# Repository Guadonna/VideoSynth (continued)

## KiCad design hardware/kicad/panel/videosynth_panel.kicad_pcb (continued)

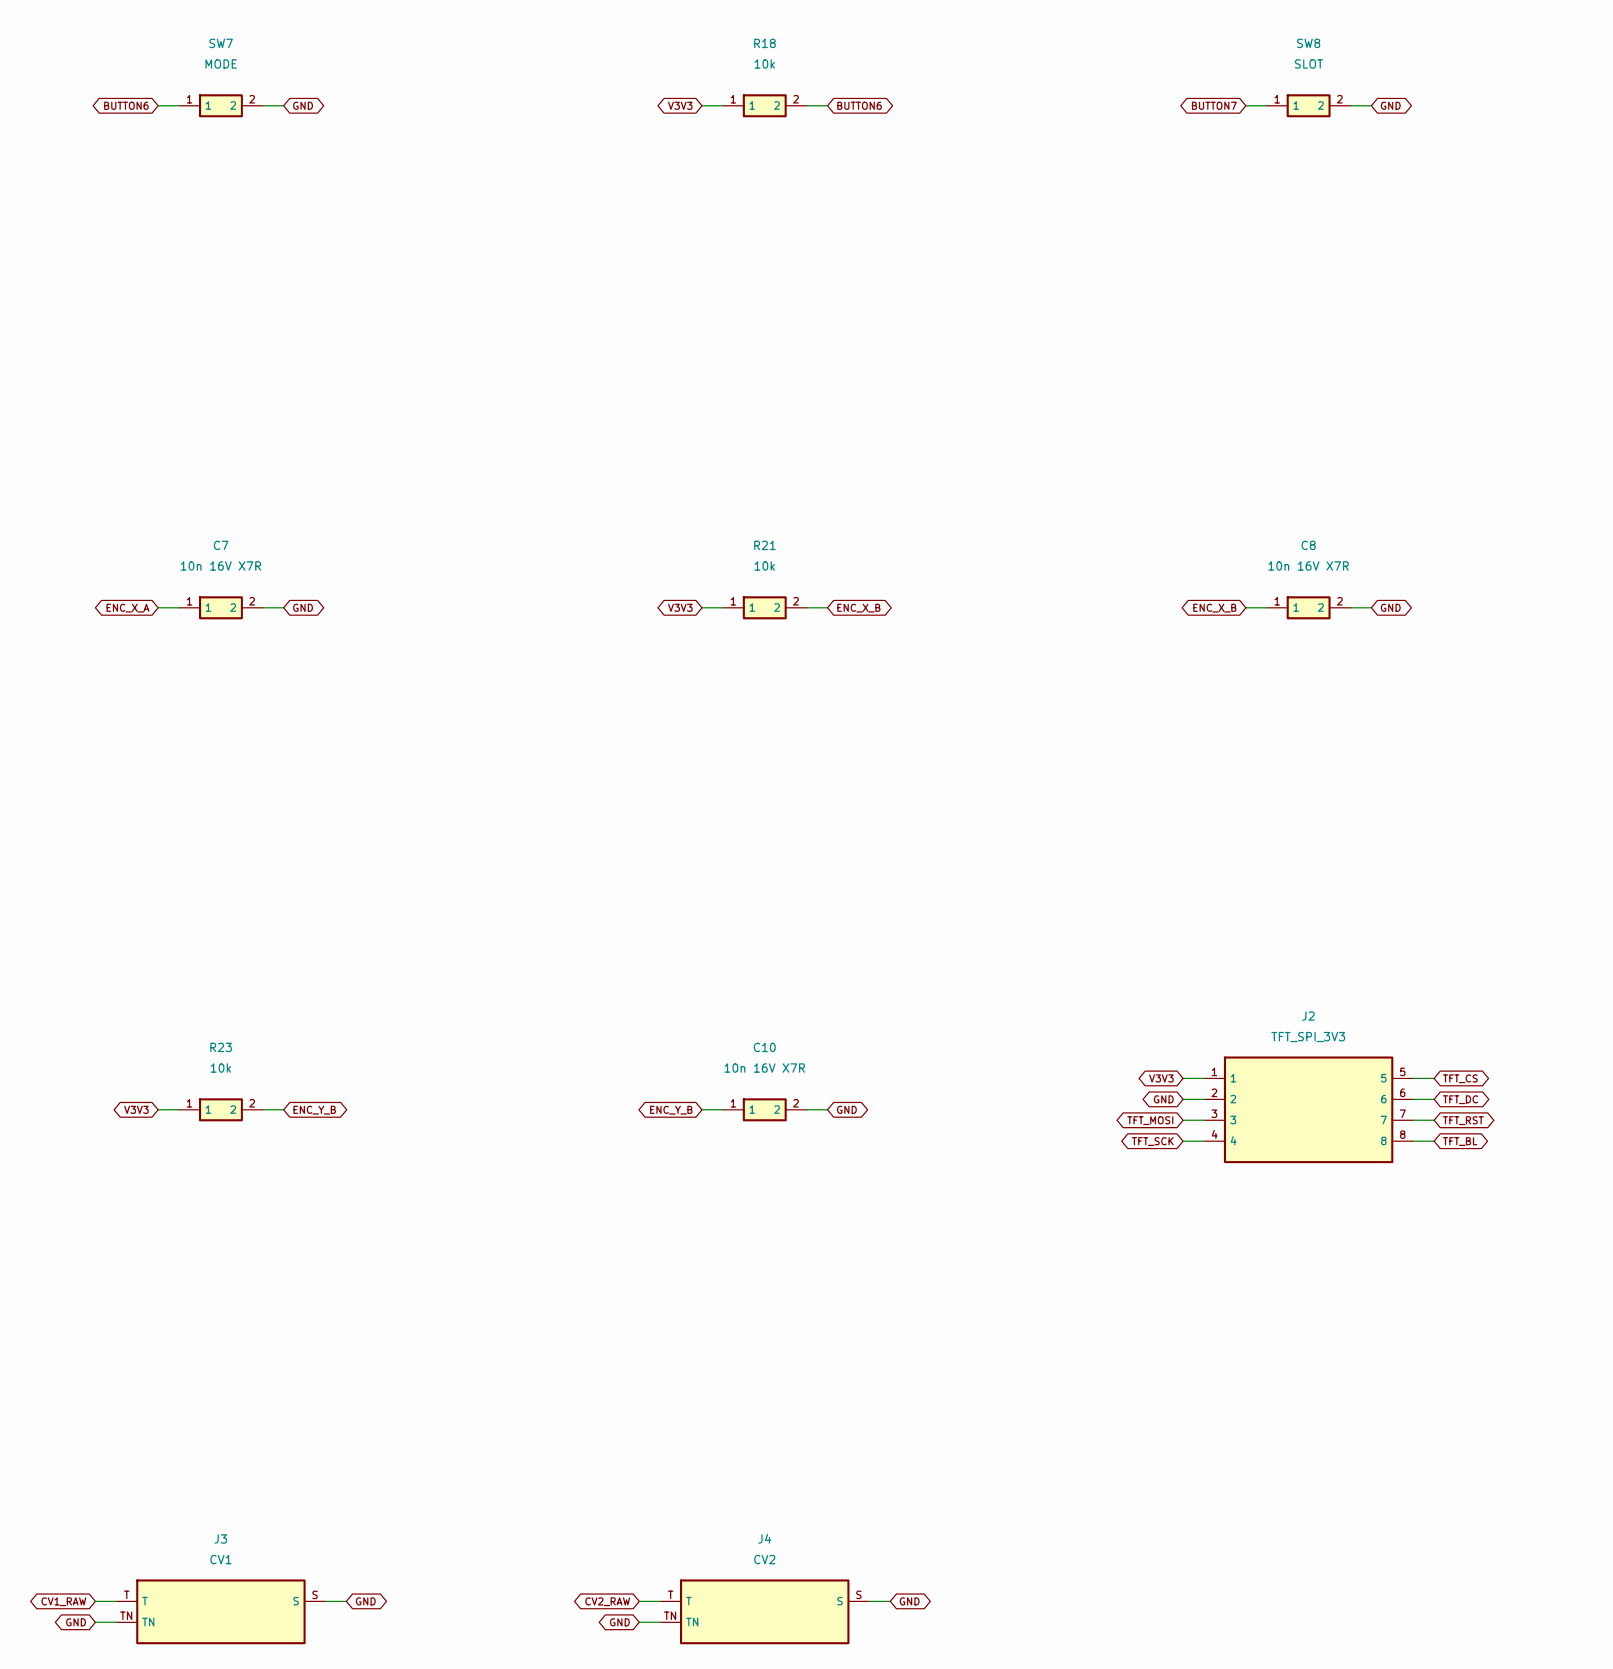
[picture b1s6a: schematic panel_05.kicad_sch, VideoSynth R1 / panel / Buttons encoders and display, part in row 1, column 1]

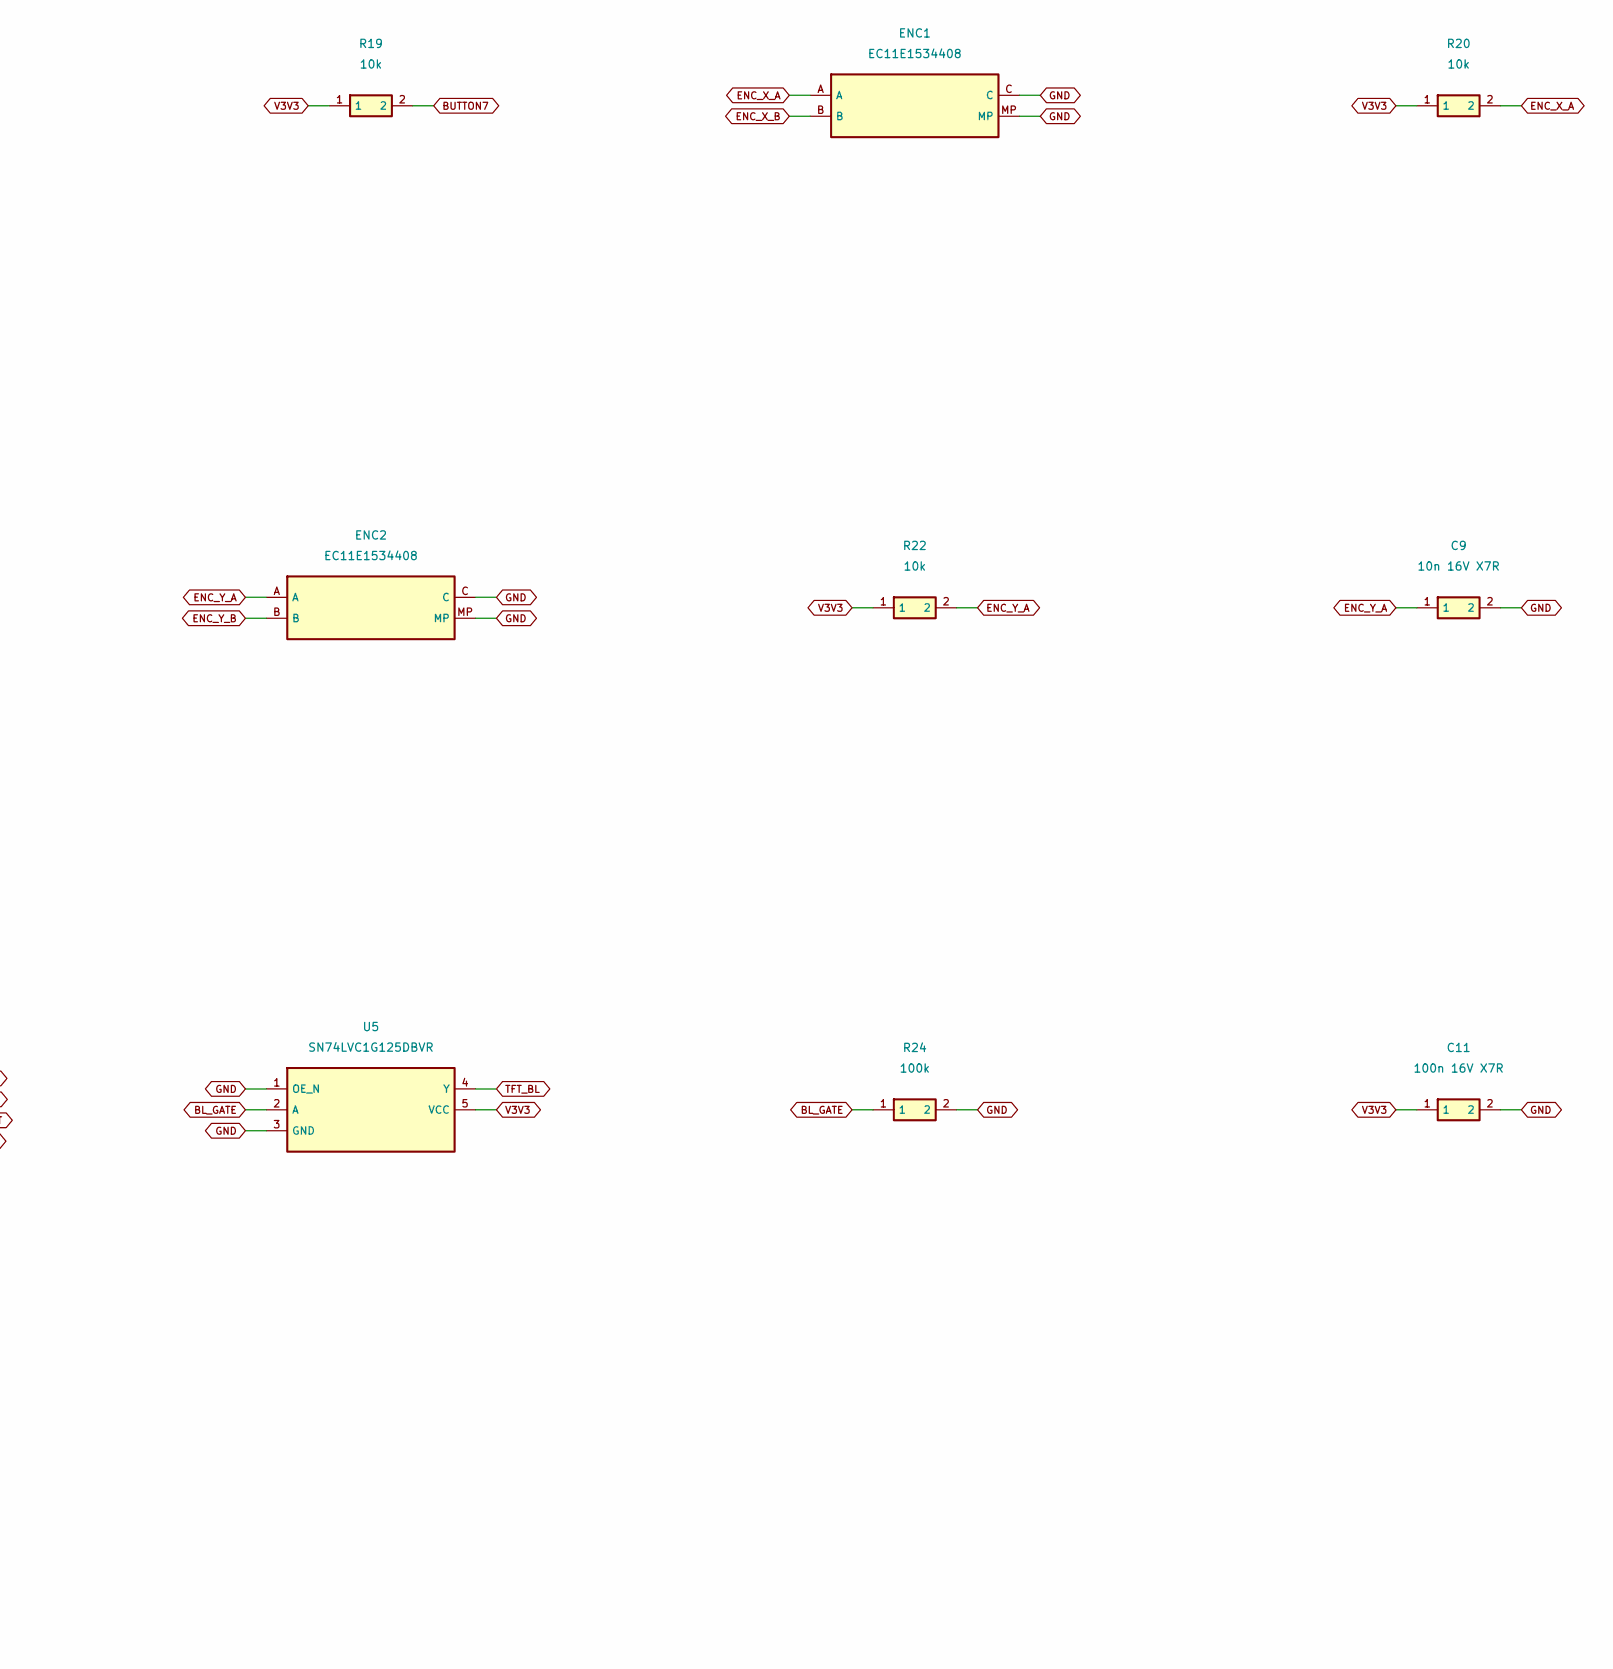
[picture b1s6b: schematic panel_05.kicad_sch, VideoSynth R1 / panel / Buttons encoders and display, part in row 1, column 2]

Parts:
C7, C8, C9, C10: 10n 16V X7R; C_0805_2012Metric
C11: 100n 16V X7R; C_0805_2012Metric
ENC1, ENC2: EC11E1534408; RotaryEncoder_Alps_EC11E_Vertical_H20mm
J2: TFT_SPI_3V3; PinHeader_1x08_P2.54mm_Vertical
J3: CV1; Jack_3.5mm_QingPu_WQP-PJ398SM_Vertical_CircularHoles
J4: CV2; Jack_3.5mm_QingPu_WQP-PJ398SM_Vertical_CircularHoles
R18, R19, R20, R21, R22, R23: 10k; R_0805_2012Metric
R24: 100k; R_0805_2012Metric
SW7: MODE; SW_PUSH_6mm
SW8: SLOT; SW_PUSH_6mm
U5: SN74LVC1G125DBVR; SOT-23-5

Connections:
BL_GATE: R24.1, U5.2 (A); also elsewhere on the board
BUTTON6: R18.2, SW7.1; also elsewhere on the board
BUTTON7: R19.2, SW8.1; also elsewhere on the board
CV1_RAW: J3.T; also elsewhere on the board
CV2_RAW: J4.T; also elsewhere on the board
ENC_X_A: C7.1, ENC1.A, R20.2; also elsewhere on the board
ENC_X_B: C8.1, ENC1.B, R21.2; also elsewhere on the board
ENC_Y_A: C9.1, ENC2.A, R22.2; also elsewhere on the board
ENC_Y_B: C10.1, ENC2.B, R23.2; also elsewhere on the board
GND: C7.2, C8.2, C9.2, C10.2, C11.2, ENC1.C, ENC1.MP, ENC2.C, ENC2.MP, J2.2, J3.S, J3.TN, J4.S, J4.TN, R24.2, SW7.2, SW8.2, U5.1 (OE_N), U5.3 (GND); also elsewhere on the board
TFT_BL: J2.8, U5.4 (Y)
TFT_CS: J2.5; also elsewhere on the board
TFT_DC: J2.6; also elsewhere on the board
TFT_MOSI: J2.3; also elsewhere on the board
TFT_RST: J2.7; also elsewhere on the board
TFT_SCK: J2.4; also elsewhere on the board
V3V3: C11.1, J2.1, R18.1, R19.1, R20.1, R21.1, R22.1, R23.1, U5.5 (VCC); also elsewhere on the board

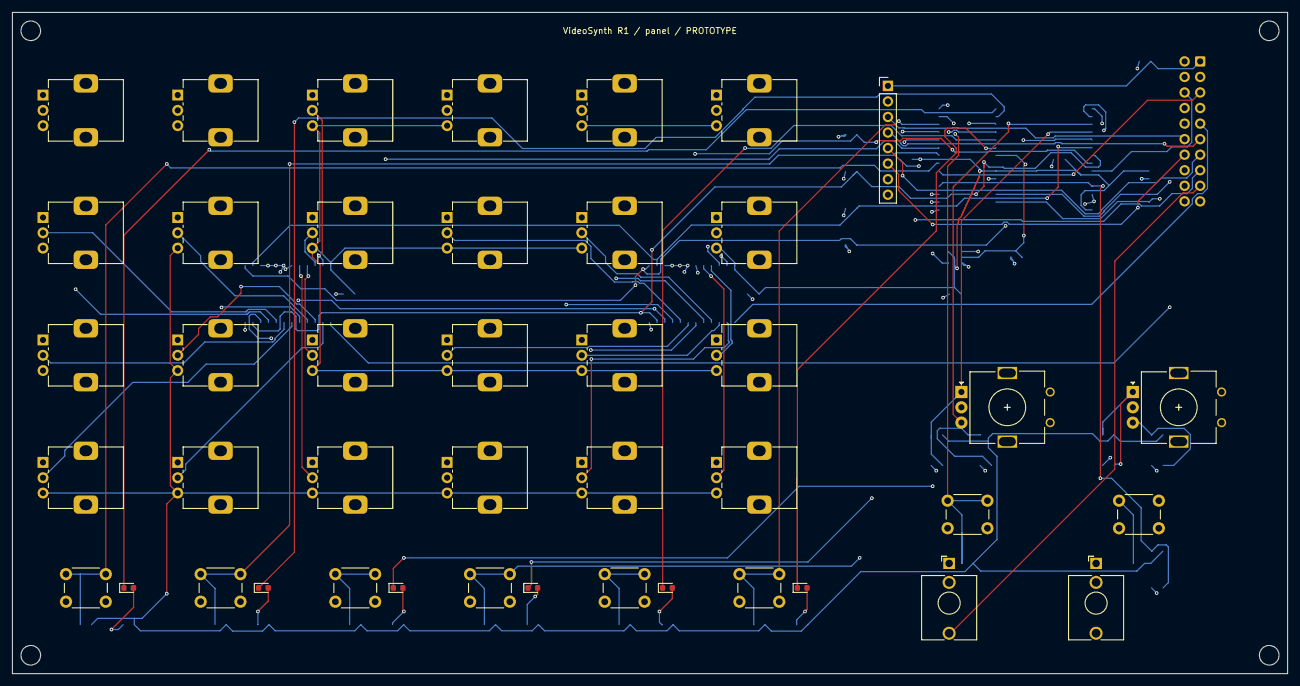
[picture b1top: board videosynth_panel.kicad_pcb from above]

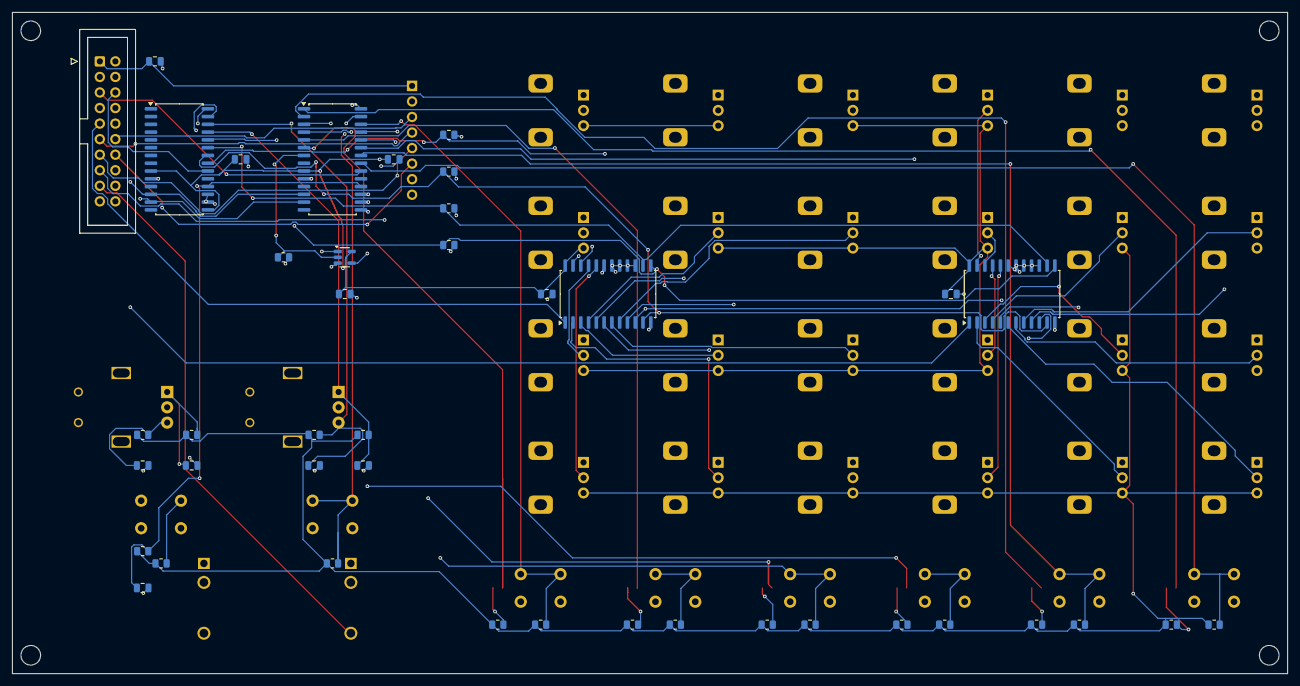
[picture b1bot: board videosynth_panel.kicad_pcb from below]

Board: 4 copper layers, 208.3 x 108.0 mm, 88 parts (41 on the bottom side), 70 nets.

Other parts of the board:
H1, H2, H3, H4: MountingHole_3.2mm_M3

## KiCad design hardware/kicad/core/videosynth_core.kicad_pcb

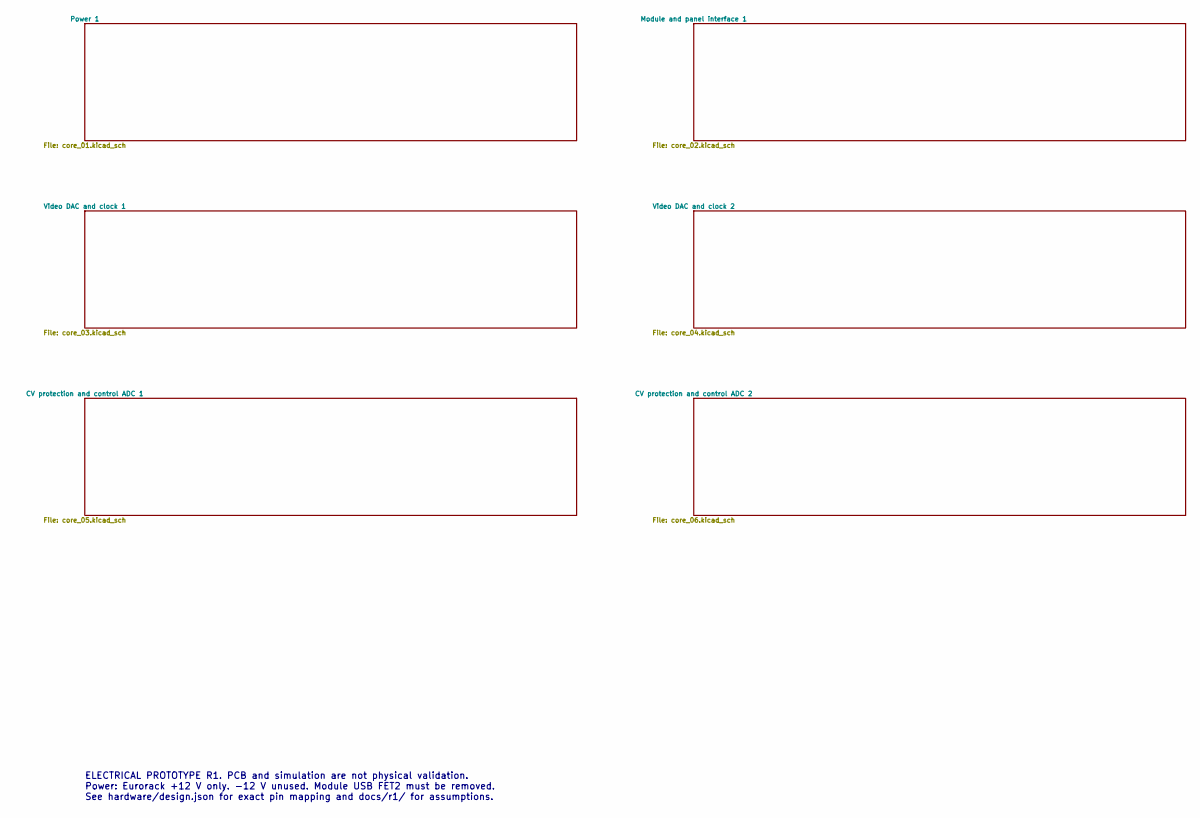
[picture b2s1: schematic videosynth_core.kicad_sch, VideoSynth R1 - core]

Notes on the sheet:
ELECTRICAL PROTOTYPE R1. PCB and simulation are not physical validation. Power: Eurorack +12 V only. -12 V unused. Module USB FET2 must be removed. See hardware/design.json for exact pin mapping and docs/r1/ for assumptions.

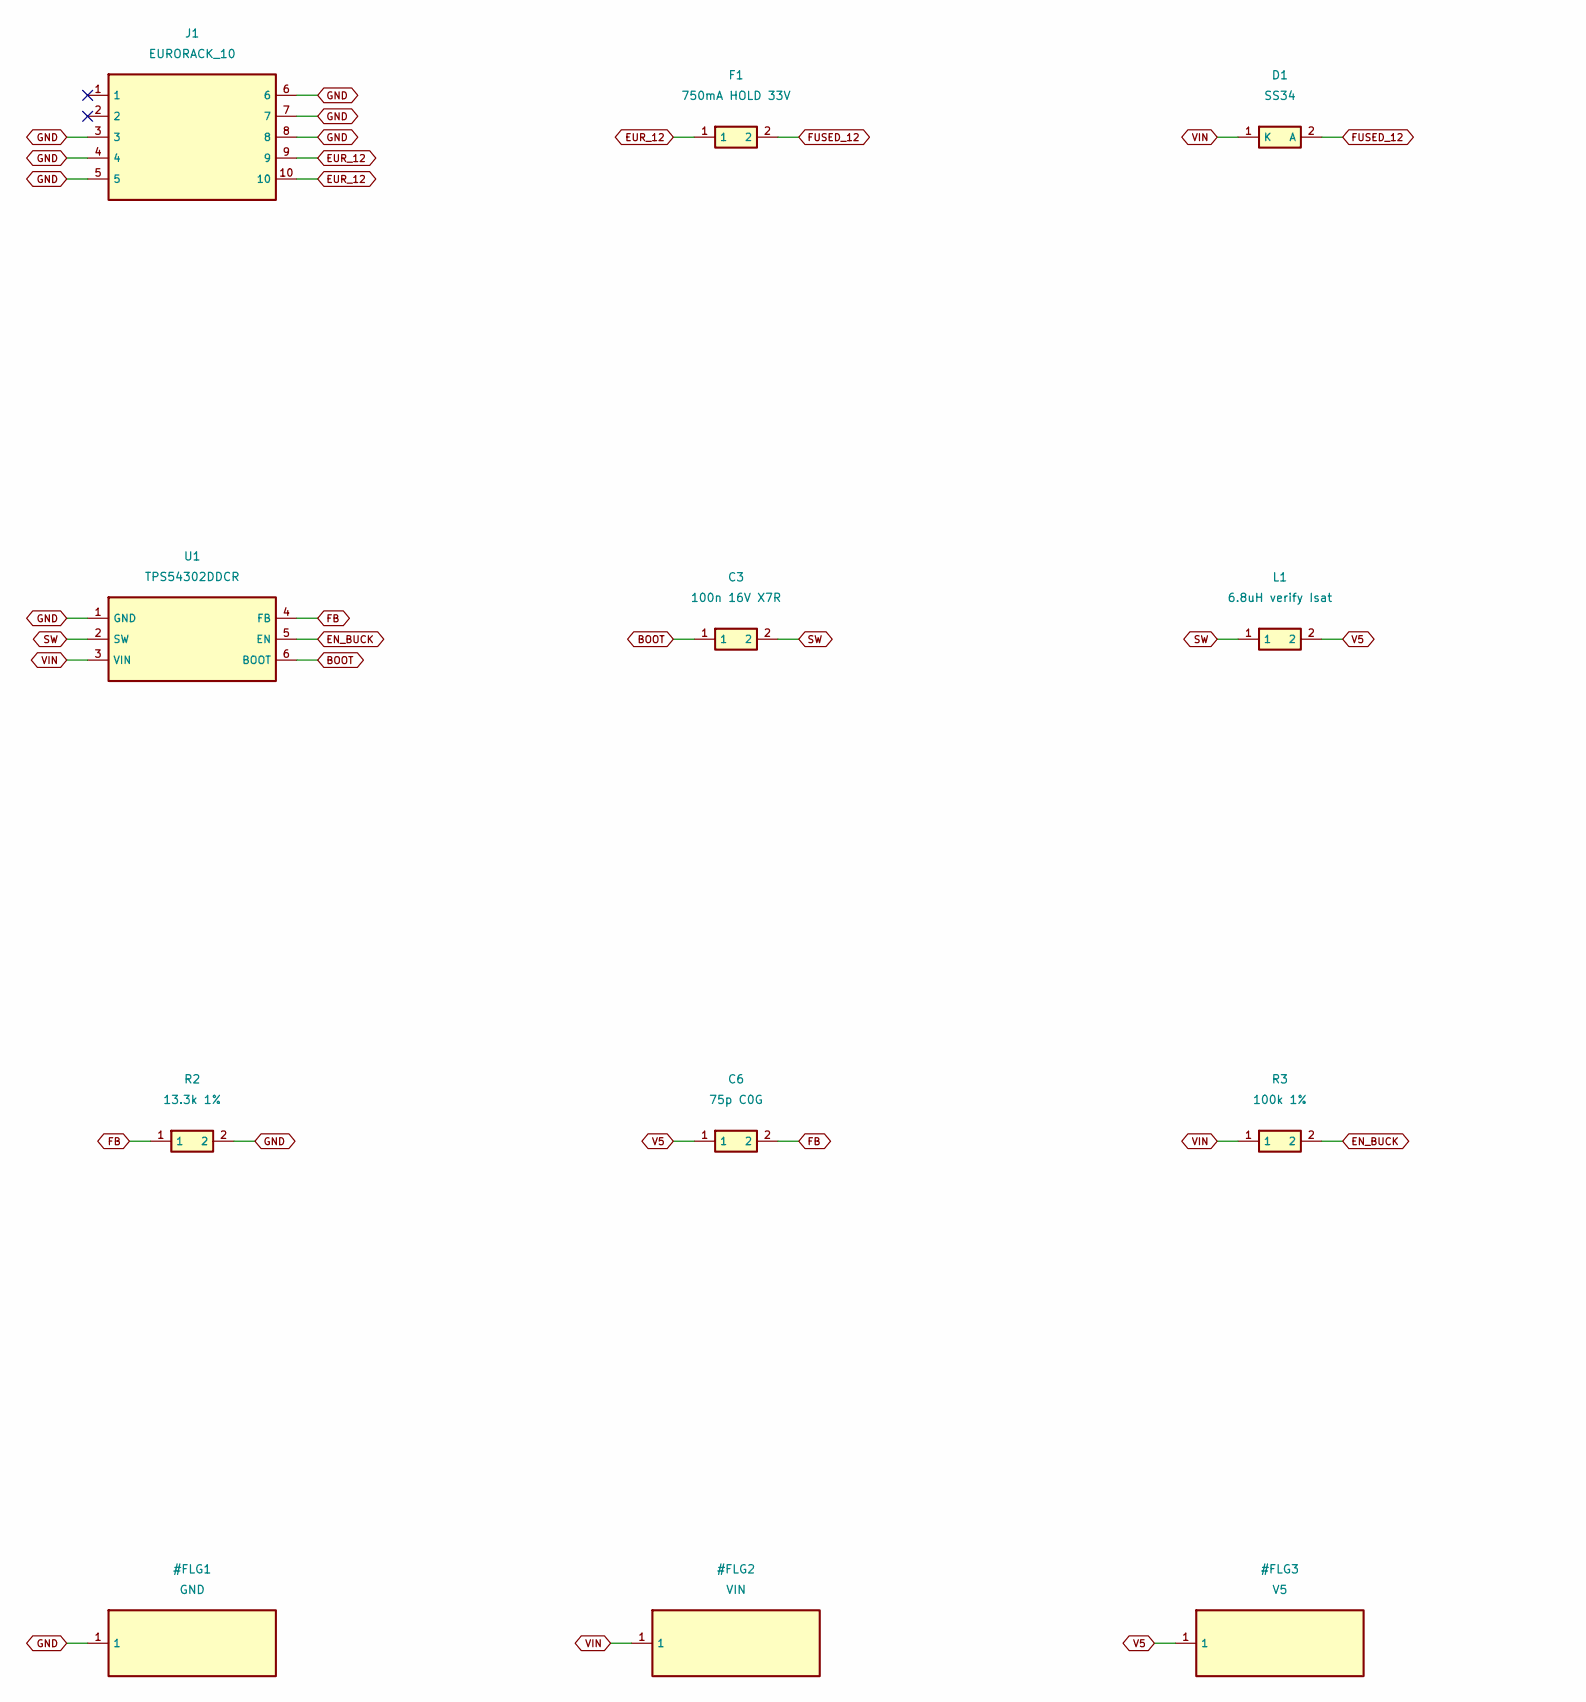
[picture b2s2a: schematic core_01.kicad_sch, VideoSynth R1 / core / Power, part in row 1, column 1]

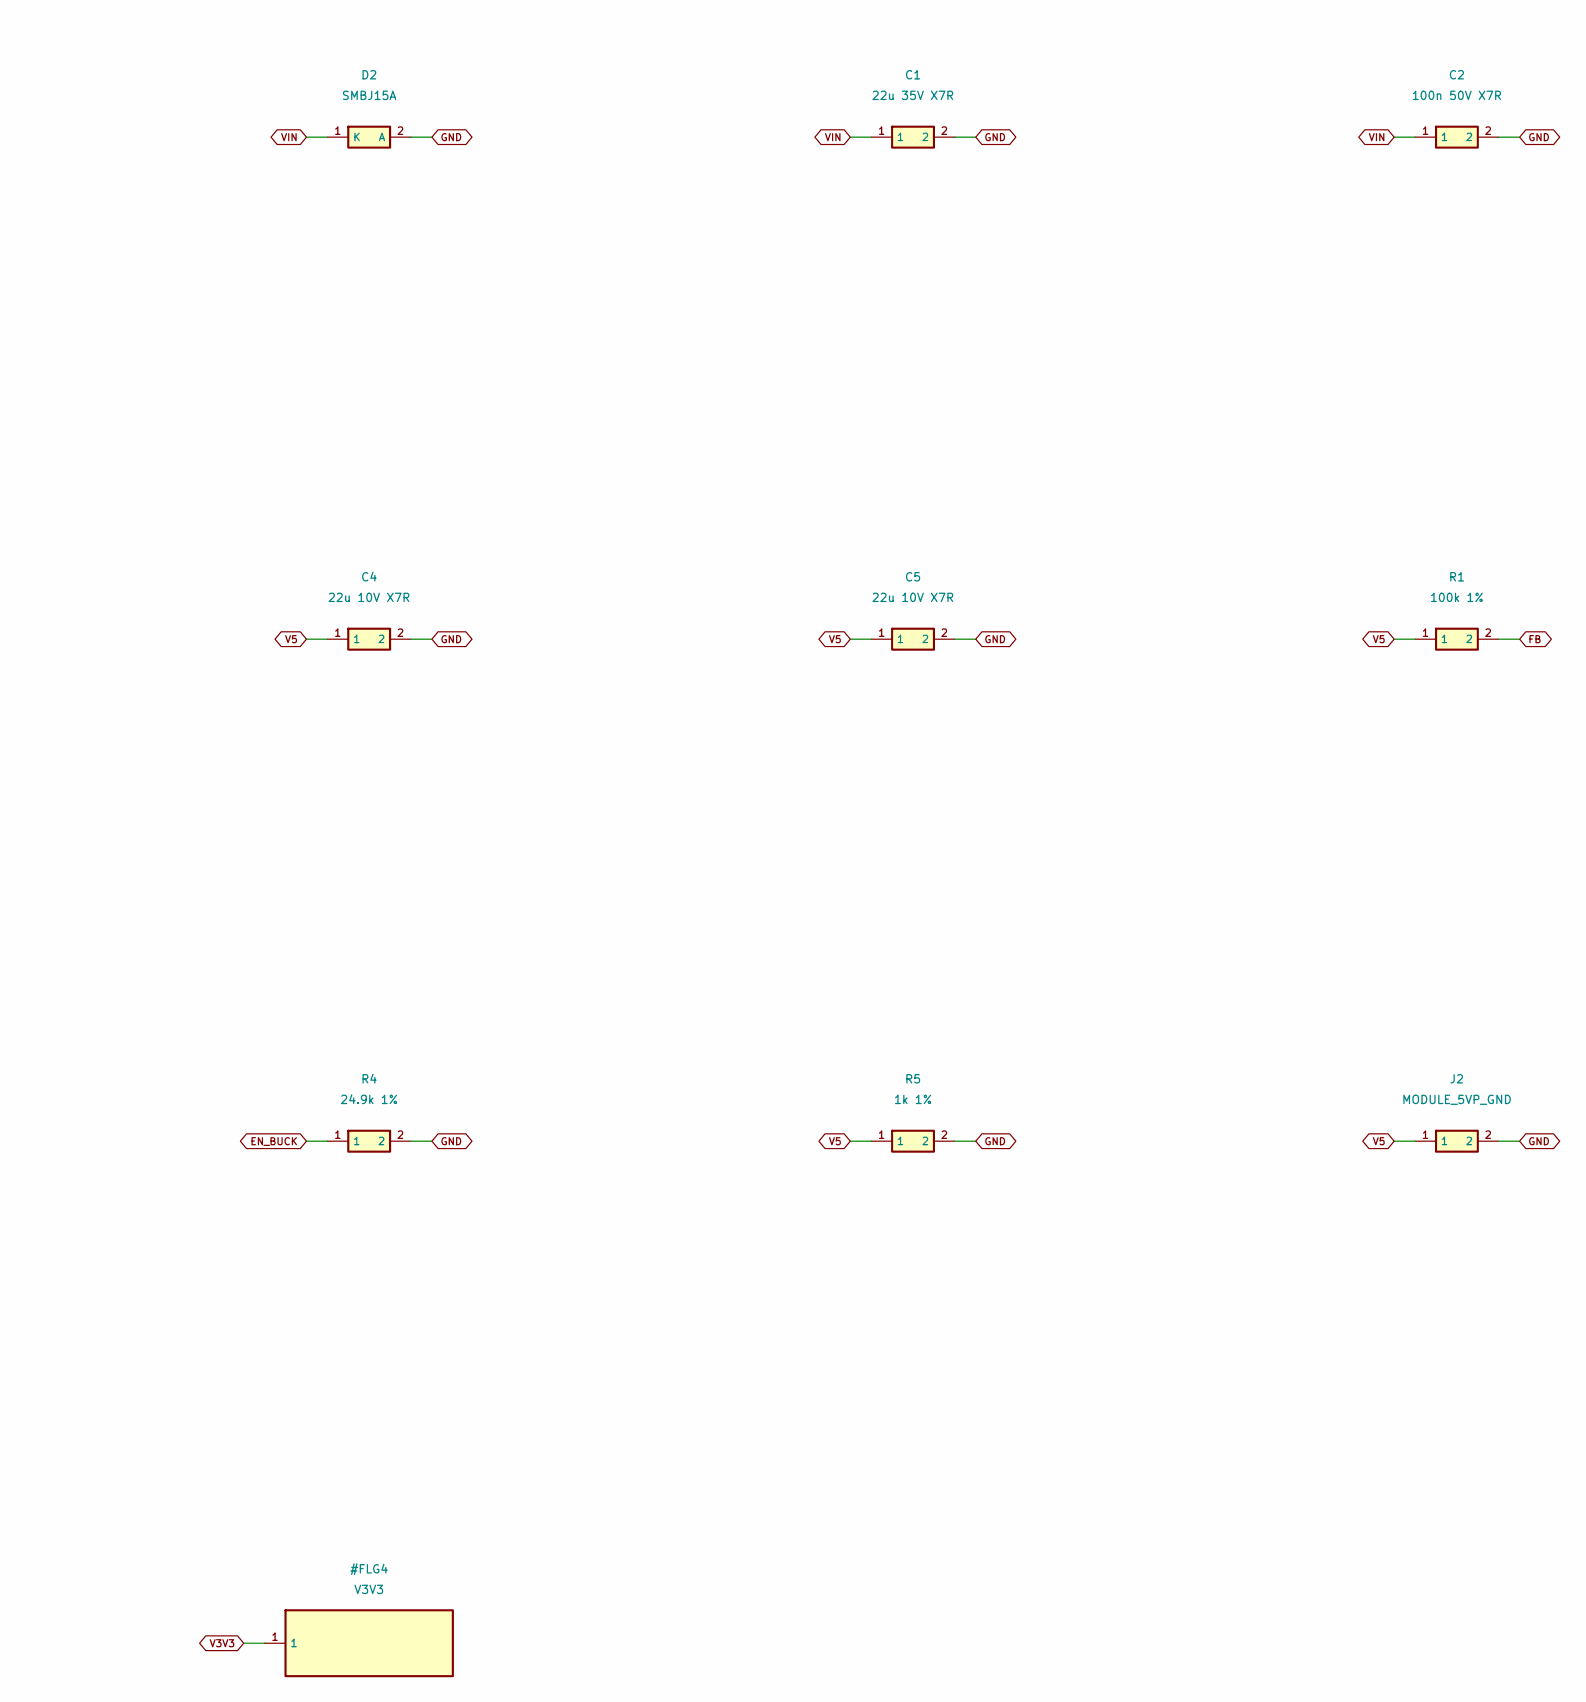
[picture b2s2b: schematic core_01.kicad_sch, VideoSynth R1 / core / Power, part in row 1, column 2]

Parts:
C1: 22u 35V X7R; C_1210_3225Metric
C2: 100n 50V X7R; C_0805_2012Metric
C3: 100n 16V X7R; C_0805_2012Metric
C4, C5: 22u 10V X7R; C_0805_2012Metric
C6: 75p C0G; C_0805_2012Metric
D1: SS34; D_SMA
D2: SMBJ15A; D_SMB
F1: 750mA HOLD 33V; Fuse_1812_4532Metric
J1: EURORACK_10; IDC-Header_2x05_P2.54mm_Vertical
J2: MODULE_5VP_GND; PinHeader_1x02_P2.54mm_Vertical
L1: 6.8uH verify Isat; L_Bourns_SRP7028A_7.3x6.6mm
R1, R3: 100k 1%; R_0805_2012Metric
R2: 13.3k 1%; R_0805_2012Metric
R4: 24.9k 1%; R_0805_2012Metric
R5: 1k 1%; R_0805_2012Metric
U1: TPS54302DDCR; SOT-23-6

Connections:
BOOT: C3.1, U1.6 (BOOT)
EN_BUCK: R3.2, R4.1, U1.5 (EN)
EUR_12: F1.1, J1.9, J1.10
FB: C6.2, R1.2, R2.1, U1.4 (FB)
FUSED_12: D1.2 (A), F1.2
GND: C1.2, C2.2, C4.2, C5.2, D2.2 (A), J1.3, J1.4, J1.5, J1.6, J1.7, J1.8, J2.2, R2.2, R4.2, R5.2, U1.1 (GND); also elsewhere on the board
SW: C3.2, L1.1, U1.2 (SW)
V5: C4.1, C5.1, C6.1, J2.1, L1.2, R1.1, R5.1; also elsewhere on the board
VIN: C1.1, C2.1, D1.1 (K), D2.1 (K), R3.1, U1.3 (VIN)

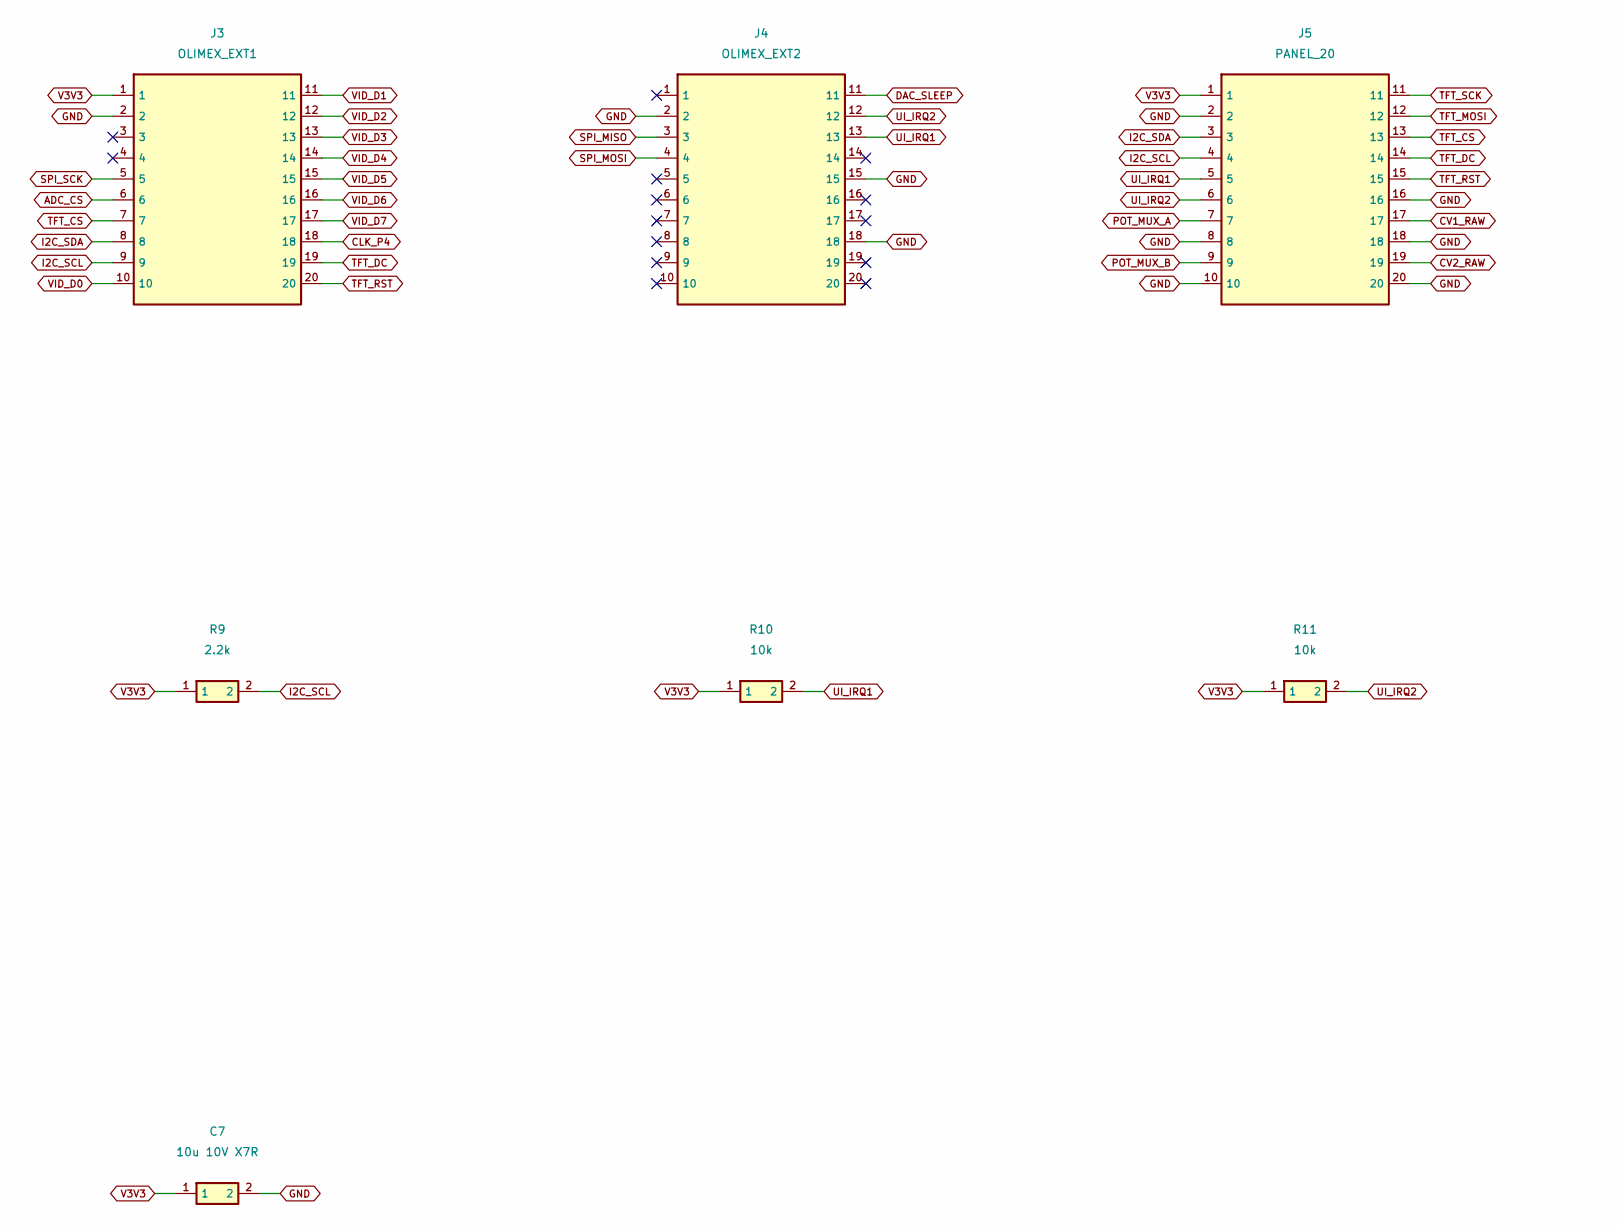
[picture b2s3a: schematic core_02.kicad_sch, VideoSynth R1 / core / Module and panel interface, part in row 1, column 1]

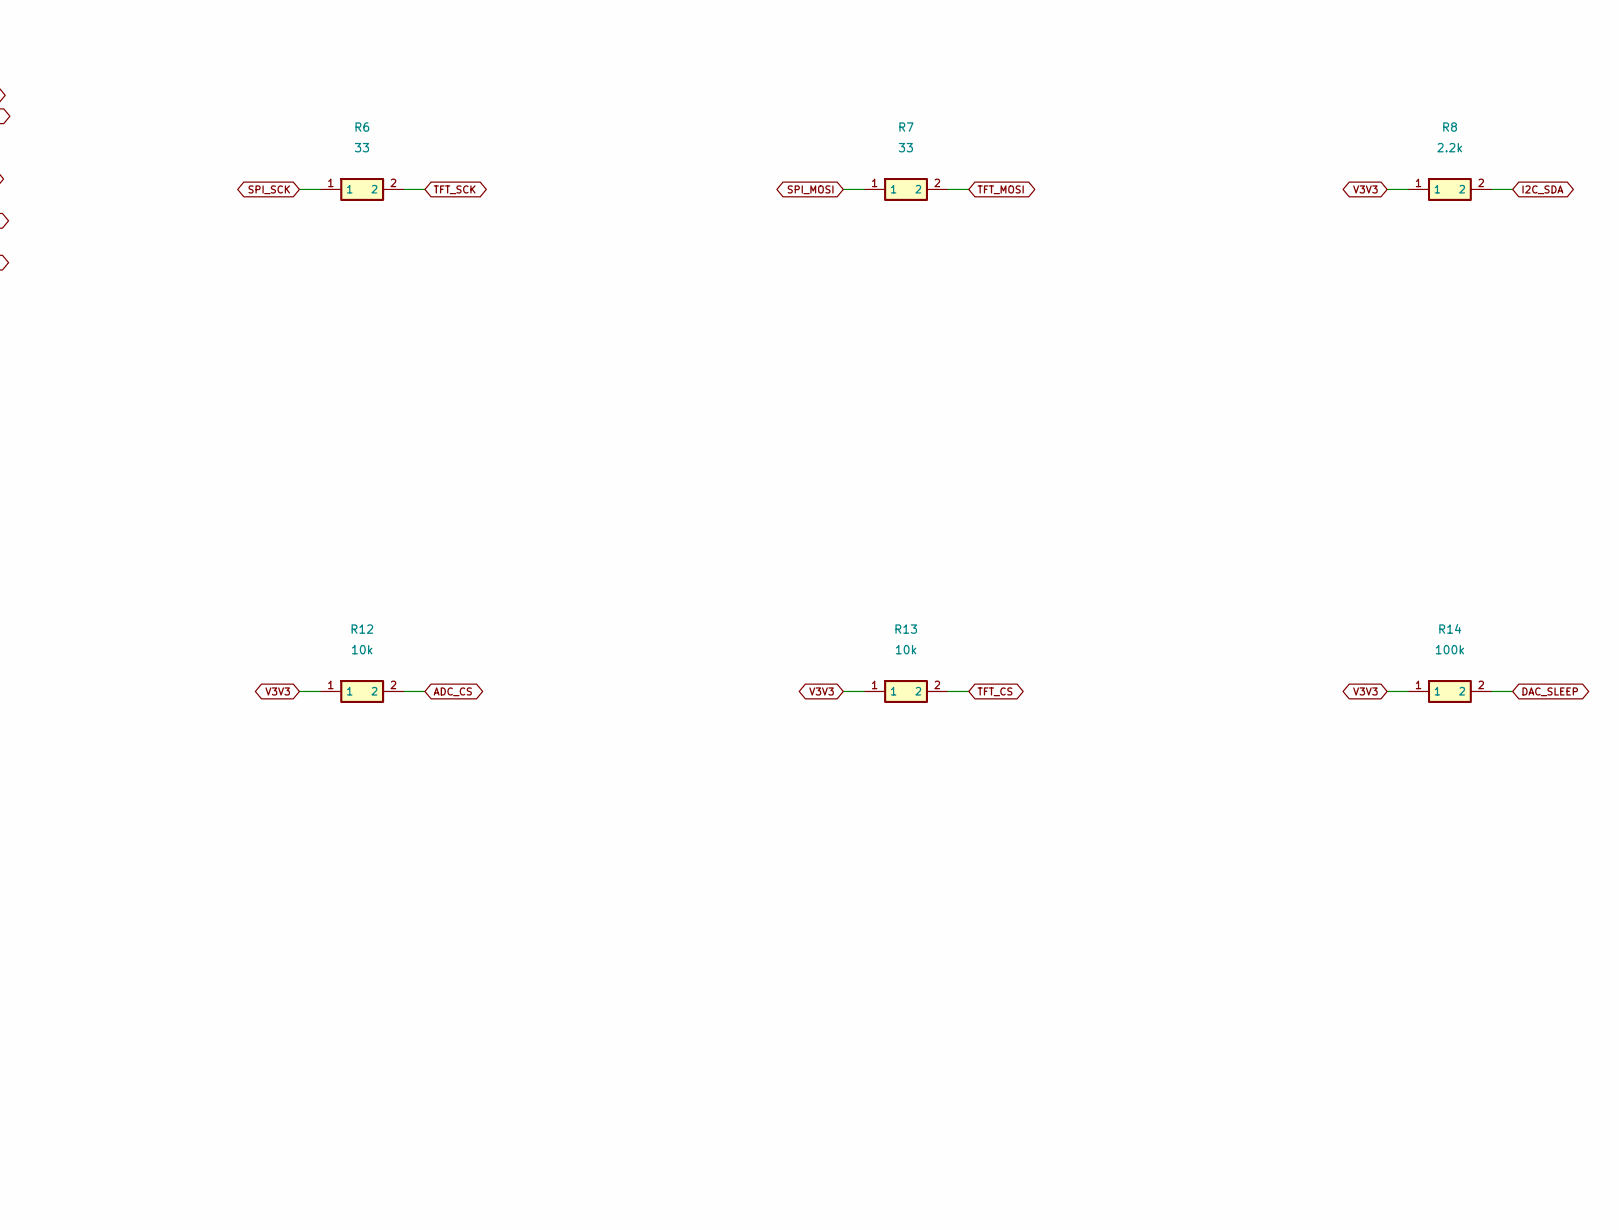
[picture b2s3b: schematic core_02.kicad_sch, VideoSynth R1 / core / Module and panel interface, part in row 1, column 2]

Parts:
C7: 10u 10V X7R; C_0805_2012Metric
J3: OLIMEX_EXT1; PinSocket_1x20_P2.54mm_Vertical
J4: OLIMEX_EXT2; PinSocket_1x20_P2.54mm_Vertical
J5: PANEL_20; IDC-Header_2x10_P2.54mm_Vertical
R6, R7: 33; R_0805_2012Metric
R8, R9: 2.2k; R_0805_2012Metric
R10, R11, R12, R13: 10k; R_0805_2012Metric
R14: 100k; R_0805_2012Metric

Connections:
ADC_CS: J3.6, R12.2; also elsewhere on the board
CLK_P4: J3.18; also elsewhere on the board
CV1_RAW: J5.17; also elsewhere on the board
CV2_RAW: J5.19; also elsewhere on the board
DAC_SLEEP: J4.11, R14.2; also elsewhere on the board
GND: C7.2, J3.2, J4.2, J4.15, J4.18, J5.2, J5.8, J5.10, J5.16, J5.18, J5.20; also elsewhere on the board
I2C_SCL: J3.9, J5.4, R9.2
I2C_SDA: J3.8, J5.3, R8.2
POT_MUX_A: J5.7; also elsewhere on the board
POT_MUX_B: J5.9; also elsewhere on the board
SPI_MISO: J4.3; also elsewhere on the board
SPI_MOSI: J4.4, R7.1; also elsewhere on the board
SPI_SCK: J3.5, R6.1; also elsewhere on the board
TFT_CS: J3.7, J5.13, R13.2
TFT_DC: J3.19, J5.14
TFT_MOSI: J5.12, R7.2
TFT_RST: J3.20, J5.15
TFT_SCK: J5.11, R6.2
UI_IRQ1: J4.13, J5.5, R10.2
UI_IRQ2: J4.12, J5.6, R11.2
V3V3: C7.1, J3.1, J5.1, R8.1, R9.1, R10.1, R11.1, R12.1, R13.1, R14.1; also elsewhere on the board
VID_D0: J3.10; also elsewhere on the board
VID_D1: J3.11; also elsewhere on the board
VID_D2: J3.12; also elsewhere on the board
VID_D3: J3.13; also elsewhere on the board
VID_D4: J3.14; also elsewhere on the board
VID_D5: J3.15; also elsewhere on the board
VID_D6: J3.16; also elsewhere on the board
VID_D7: J3.17; also elsewhere on the board
